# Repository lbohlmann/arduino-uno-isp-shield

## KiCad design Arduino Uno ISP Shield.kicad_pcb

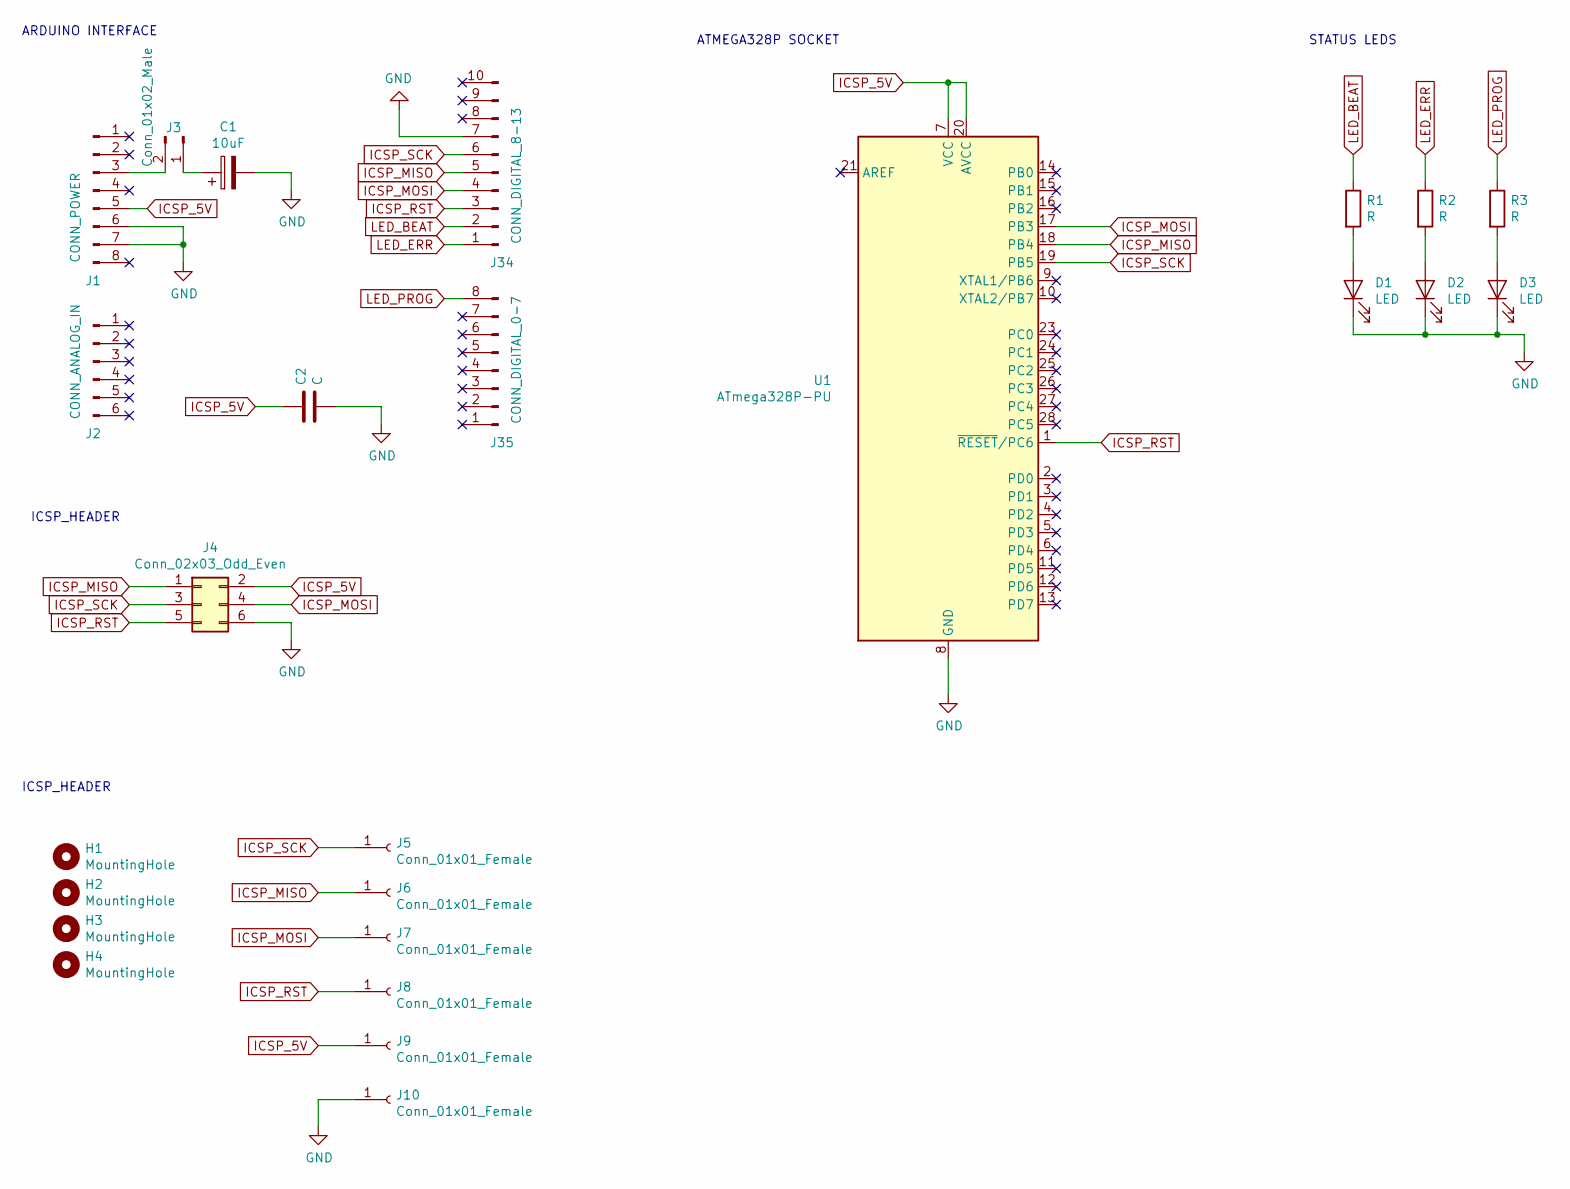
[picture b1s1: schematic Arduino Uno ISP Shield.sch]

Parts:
C1: 10uF; CP_Elec_5x5.3
C2: C; C_0805_2012Metric
D1, D2, D3: LED; LED_0805_2012Metric
H1, H2, H3, H4: MountingHole; MountingHole_2.2mm_M2
J1: CONN_POWER; PinHeader_1x08_P2.54mm_Vertical
J2: CONN_ANALOG_IN; PinHeader_1x06_P2.54mm_Vertical
J3: Conn_01x02_Male; PinHeader_1x02_P2.54mm_Vertical
J4: Conn_02x03_Odd_Even; PinHeader_2x03_P2.54mm_Vertical
J5, J6, J7, J8, J9, J10: Conn_01x01_Female; SolderWirePad_1x01_Drill1.2mm
J34: CONN_DIGITAL_8-13; PinHeader_1x10_P2.54mm_Vertical
J35: CONN_DIGITAL_0-7; PinHeader_1x08_P2.54mm_Vertical
R1, R2, R3: R; R_0805_2012Metric
U1: ATmega328P-PU; DIP-28_W7.62mm

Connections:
GND: C1.2, C2.2, D1.1 (K), D2.1 (K), D3.1 (K), J1.6, J1.7, J4.6, J10.1, J34.7, U1.8 (GND), U1.22 (GND)
ICSP_5V: C2.1, J1.5, J4.2, J9.1, U1.7 (VCC), U1.20 (AVCC)
ICSP_MISO: J4.1, J6.1, J34.5, U1.18 (PB4)
ICSP_MOSI: J4.4, J7.1, J34.4, U1.17 (PB3)
ICSP_RST: J4.5, J8.1, J34.3, U1.1 (~RESET~/PC6)
ICSP_SCK: J4.3, J5.1, J34.6, U1.19 (PB5)
LED_BEAT: J34.2, R1.1
LED_ERR: J34.1, R2.1
LED_PROG: J35.8, R3.1
unnamed: C1.1, J3.1
unnamed: D1.2 (A), R1.2
unnamed: D2.2 (A), R2.2
unnamed: D3.2 (A), R3.2
unnamed: J1.3, J3.2

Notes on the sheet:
ARDUINO INTERFACE
ICSP_HEADER
ATMEGA328P SOCKET
STATUS LEDS

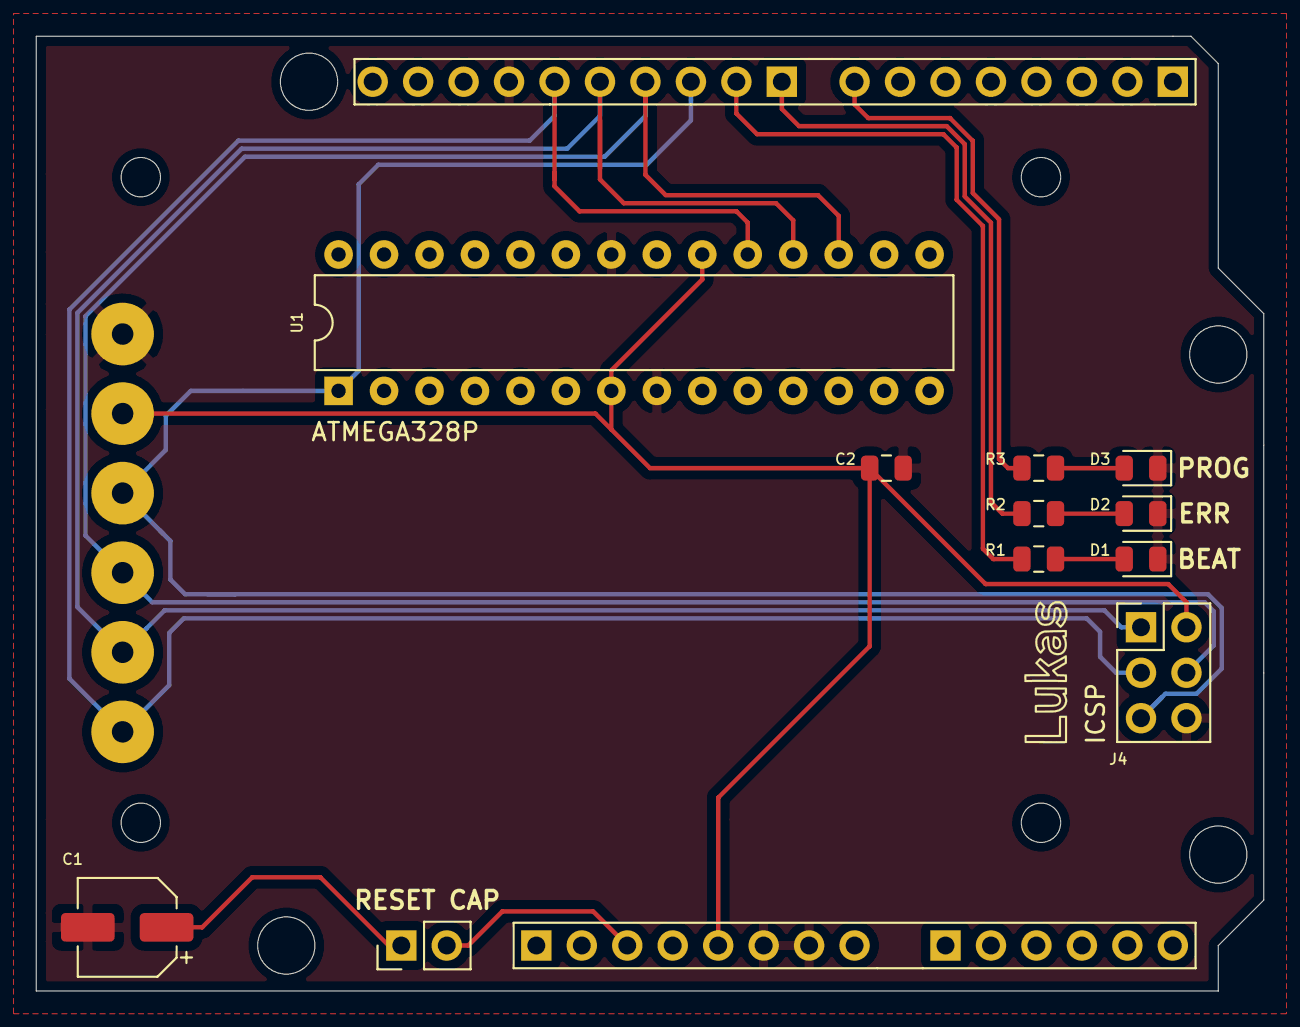
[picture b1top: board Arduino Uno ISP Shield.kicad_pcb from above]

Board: 2 copper layers, 68.6 x 53.3 mm, 25 parts (0 on the bottom side), 14 nets.

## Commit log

2021-02-12 Import KiCAD project
2021-02-12 Update gitignore
2021-02-12 Add rendering
2021-02-13 Add fabrication data
